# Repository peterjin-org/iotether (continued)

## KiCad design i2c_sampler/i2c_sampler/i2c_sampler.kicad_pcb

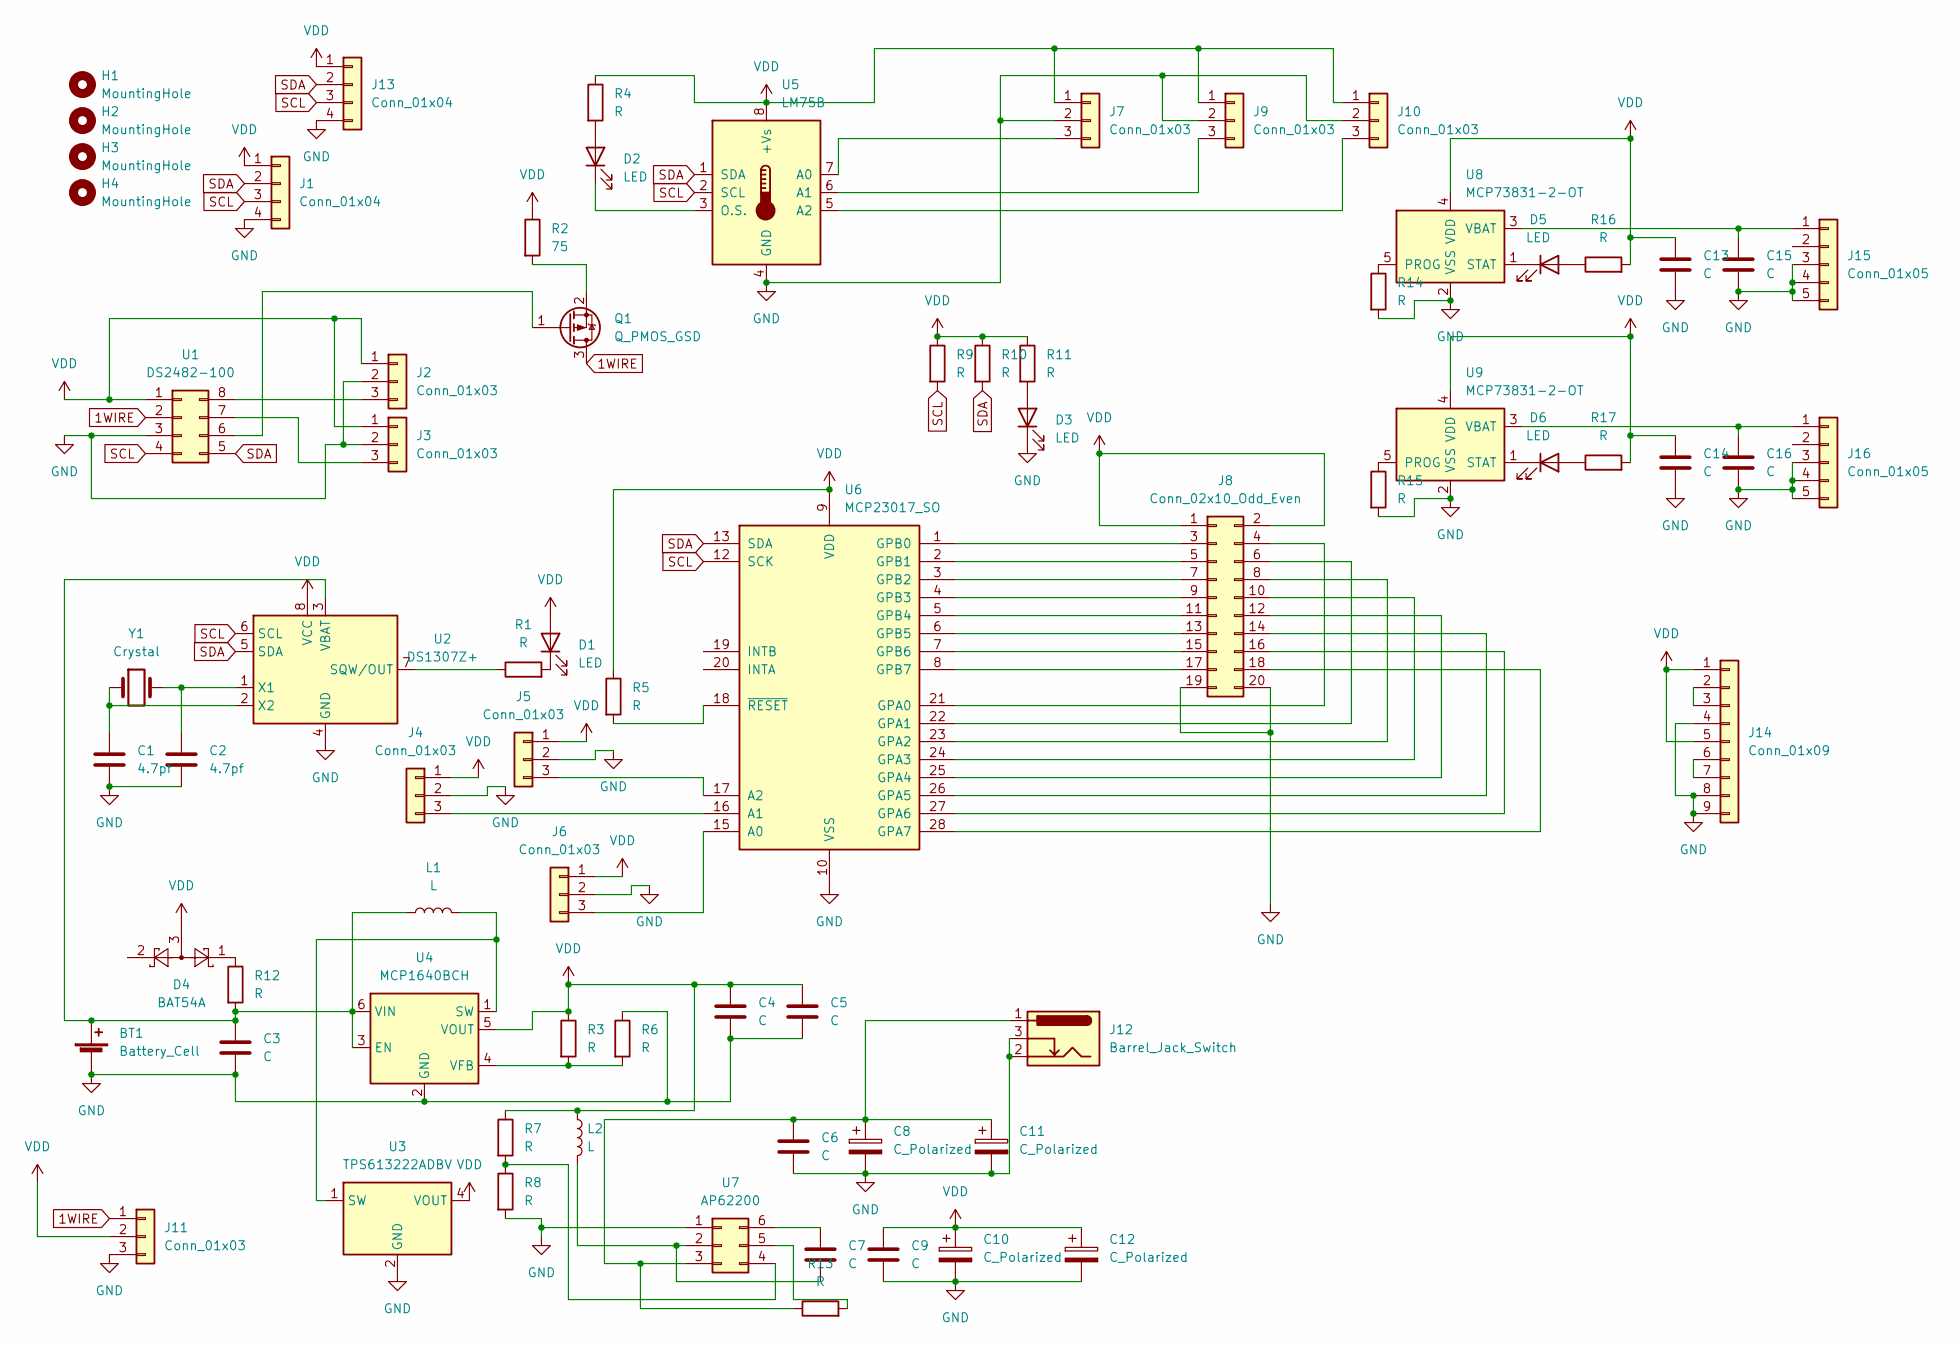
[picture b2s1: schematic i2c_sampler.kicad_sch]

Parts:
BT1: Battery_Cell; PinHeader_1x02_P2.54mm_Vertical
C1, C2: 4.7pf; C_0603_1608Metric
C3, C4, C5, C6, C7, C9, C13, C14, C15, C16: C; C_0805_2012Metric
C8, C10, C11, C12: C_Polarized; CP_Radial_D8.0mm_P3.50mm
D1, D2, D3: LED; LED_D5.0mm
D4: BAT54A; SOT-23
D5, D6: LED; LED_0603_1608Metric
H1, H2, H3, H4: MountingHole; MountingHole_3.2mm_M3
J1, J13: Conn_01x04; PinHeader_1x04_P2.54mm_Vertical
J2, J3, J4, J5, J6, J7, J9, J10: Conn_01x03; SOT-23-3
J8: Conn_02x10_Odd_Even; PinHeader_2x10_P2.54mm_Vertical
J11: Conn_01x03; PinHeader_1x03_P2.54mm_Vertical
J12: Barrel_Jack_Switch; BarrelJack_Horizontal
J14: Conn_01x09; USB_A_Wuerth_61400826021_Horizontal_Stacked
J15, J16: Conn_01x05; 009155003541006
L1: L; L_1210_3225Metric
L2: L; L_Radial_D10.5mm_P5.00mm_Abacron_AISR-01
Q1: Q_PMOS_GSD; SOT-23-3
R1, R3, R4, R5, R6, R7, R8, R9, R10, R11, R12, R13, R14, R15, R16, R17: R; R_0603_1608Metric
R2: 75; R_0805_2012Metric
U1: DS2482-100; SOIC-8_3.9x4.9mm_P1.27mm
U2: DS1307Z+; SOIC-8_3.9x4.9mm_P1.27mm
U3: TPS613222ADBV; SOT-23-5
U4: MCP1640BCH; SOT-23-6
U5: LM75B; SOIC-8_3.9x4.9mm_P1.27mm
U6: MCP23017_SO; SOIC-28W_7.5x17.9mm_P1.27mm
U7: AP62200; SOT-23-6
U8, U9: MCP73831-2-OT; SOT-23-5
Y1: Crystal; Crystal_Round_D2.0mm_Vertical

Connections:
1WIRE: J11.1, Q1.3 (D), U1.2
GND: BT1.2 (-), C1.2, C2.2, C3.2, C4.2, C5.2, C6.2, C8.2, C9.2, C10.2, C11.2, C12.2, C13.2, C14.2, C15.2, C16.2, D3.1 (K), J1.4, J2.2, J3.2, J4.2, J5.2, J6.2, J7.2, J8.19, J8.20, J9.2, J10.2, J11.3, J12.2, J12.3, J13.4, J14.4, J14.8, J14.9, J15.3, J15.4, J15.5, J16.3, J16.4, J16.5, R6.1, R8.2, R14.2, R15.2, U1.3, U2.4 (GND), U3.2 (GND), U4.2 (GND), U5.4 (GND), U6.10 (VSS), U7.1, U8.2 (VSS), U9.2 (VSS)
unnamed: BT1.1 (+), C3.1, L1.1, R12.2, U2.3 (VBAT), U4.3 (EN), U4.6 (VIN)
unnamed: C1.1, U2.2 (X2), Y1.1
unnamed: C2.1, U2.1 (X1), Y1.2
unnamed: C7.1, U7.6
unnamed: C7.2, L2.2, U7.2
unnamed: C6.1, C8.1, C11.1, J12.1, R13.1, U7.3
unnamed: C15.1, J15.1, U8.3 (VBAT)
unnamed: C16.1, J16.1, U9.3 (VBAT)
unnamed: D1.1 (K), R1.2
unnamed: D2.1 (K), U5.3 (O.S.)
unnamed: D2.2 (A), R4.2
unnamed: D3.2 (A), R11.2
unnamed: D4.1, R12.1
unnamed: D5.1 (K), U8.1 (STAT)
unnamed: D5.2 (A), R16.1
unnamed: D6.1 (K), U9.1 (STAT)
unnamed: D6.2 (A), R17.1
unnamed: J2.3, U1.8
unnamed: J3.3, U1.7
unnamed: J4.3, U6.16 (A1)
unnamed: J5.3, U6.17 (A2)
unnamed: J6.3, U6.15 (A0)
unnamed: J7.3, U5.7 (A0)
unnamed: J8.3, U6.1 (GPB0)
unnamed: J8.4, U6.21 (GPA0)
unnamed: J8.5, U6.2 (GPB1)
unnamed: J8.6, U6.22 (GPA1)
unnamed: J8.7, U6.3 (GPB2)
unnamed: J8.8, U6.23 (GPA2)
unnamed: J8.9, U6.4 (GPB3)
unnamed: J8.10, U6.24 (GPA3)
unnamed: J8.11, U6.5 (GPB4)
unnamed: J8.12, U6.25 (GPA4)
unnamed: J8.13, U6.6 (GPB5)
unnamed: J8.14, U6.26 (GPA5)
unnamed: J8.15, U6.7 (GPB6)
unnamed: J8.16, U6.27 (GPA6)
unnamed: J8.17, U6.8 (GPB7)
unnamed: J8.18, U6.28 (GPA7)
unnamed: J9.3, U5.6 (A1)
unnamed: J10.3, U5.5 (A2)
unnamed: J14.2, J14.3
unnamed: J14.6, J14.7
unnamed: L1.2, U3.1 (SW), U4.1 (SW)
unnamed: Q1.1 (G), U1.6
unnamed: Q1.2 (S), R2.2
unnamed: R1.1, U2.7 (SQW/OUT)
unnamed: R3.2, R6.2, U4.4 (VFB)
unnamed: R5.2, U6.18 (~RESET)
unnamed: R7.2, R8.1, U7.4
unnamed: R13.2, U7.5
unnamed: R14.1, U8.5 (PROG)
unnamed: R15.1, U9.5 (PROG)
SCL: J1.3, J13.3, R9.2, U1.4, U2.6 (SCL), U5.2 (SCL), U6.12 (SCK)
SDA: J1.2, J13.2, R10.2, U1.5, U2.5 (SDA), U5.1 (SDA), U6.13 (SDA)
VDD: C4.1, C5.1, C9.1, C10.1, C12.1, C13.1, C14.1, D1.2 (A), D4.3, J1.1, J2.1, J3.1, J4.1, J5.1, J6.1, J7.1, J8.1, J8.2, J9.1, J10.1, J11.2, J13.1, J14.1, J14.5, L2.1, R2.1, R3.1, R4.1, R5.1, R7.1, R9.1, R10.1, R11.1, R16.2, R17.2, U1.1, U2.8 (VCC), U3.4 (VOUT), U4.5 (VOUT), U5.8 (+Vs), U6.9 (VDD), U8.4 (VDD), U9.4 (VDD)

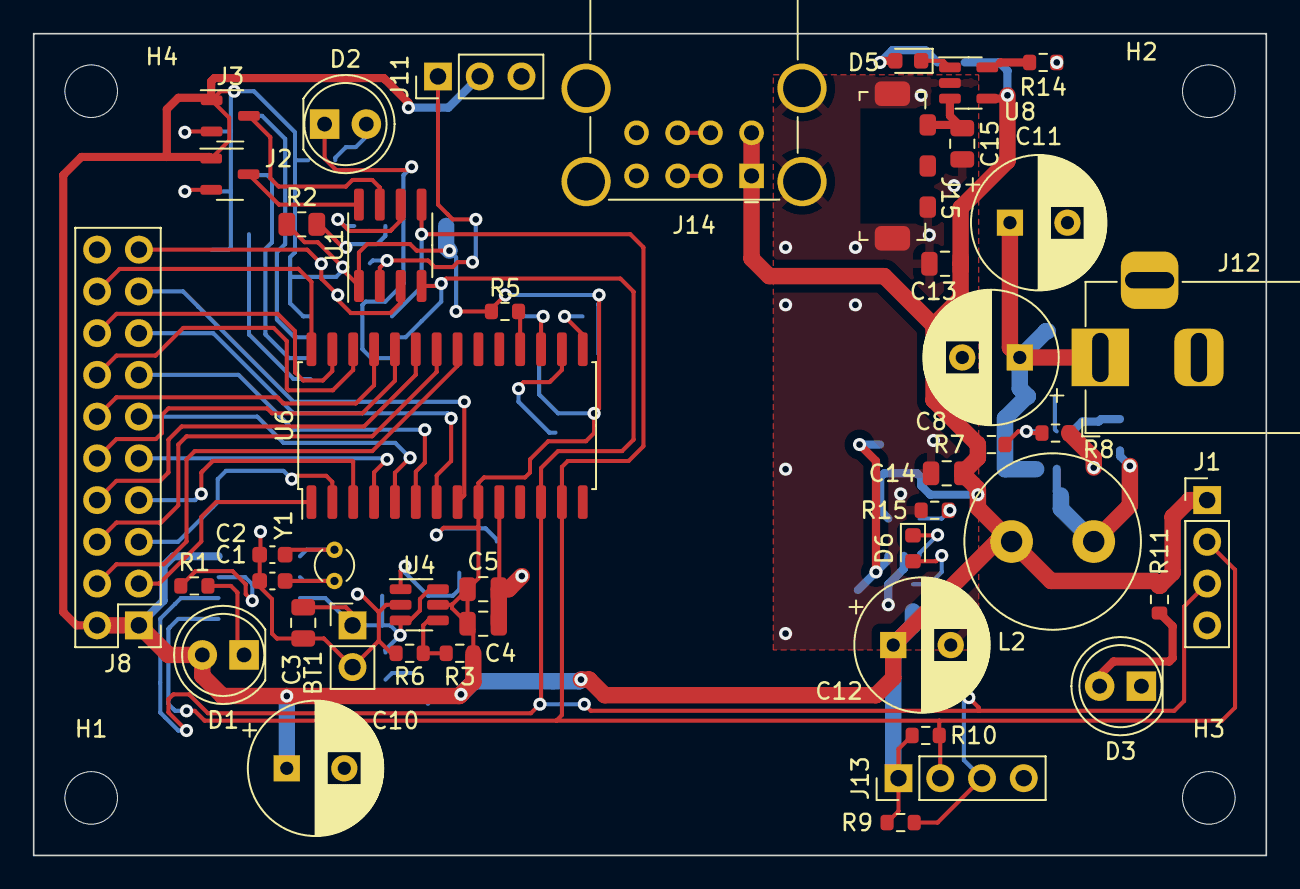
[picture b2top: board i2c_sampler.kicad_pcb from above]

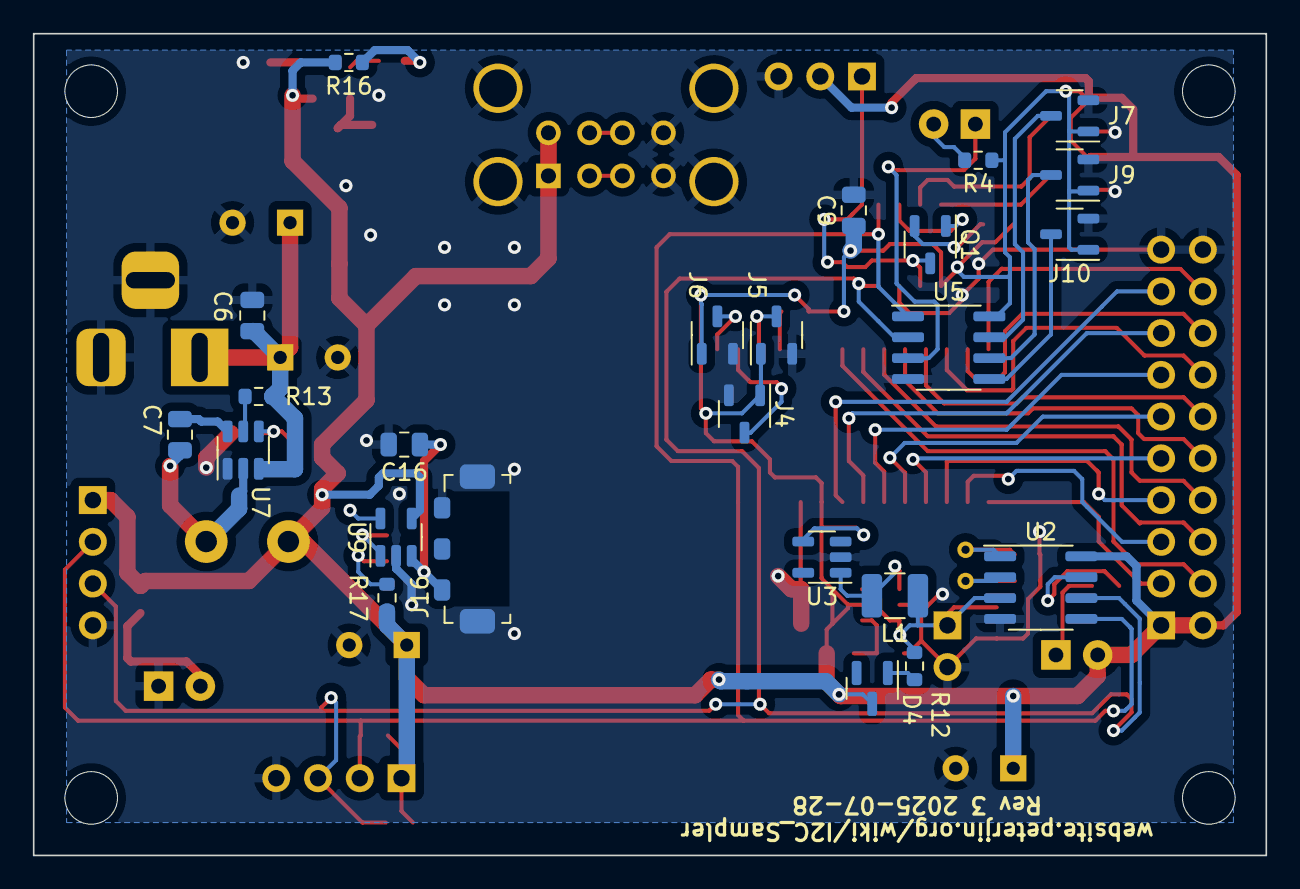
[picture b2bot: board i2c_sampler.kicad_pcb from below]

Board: 2 copper layers, 75.0 x 50.0 mm, 73 parts (24 on the bottom side), 58 nets.

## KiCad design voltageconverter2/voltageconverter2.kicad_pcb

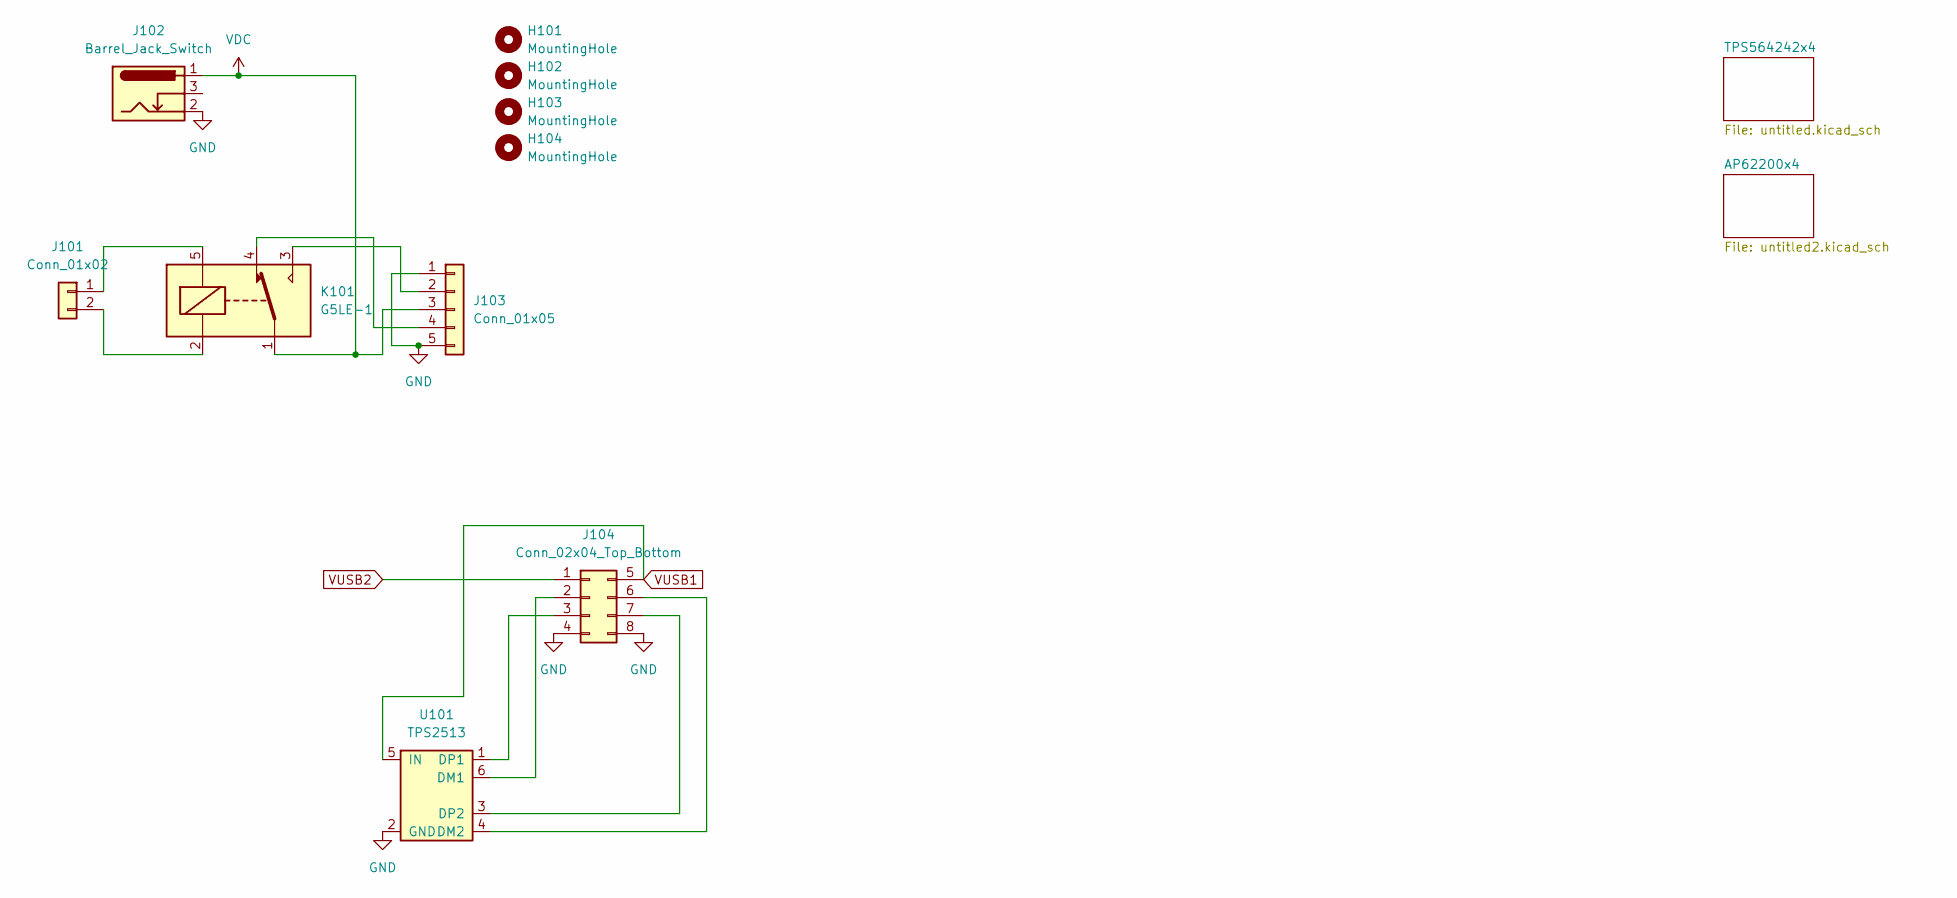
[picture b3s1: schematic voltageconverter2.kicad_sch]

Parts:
H101, H102, H103, H104: MountingHole; MountingHole_3.2mm_M3
J101: Conn_01x02; PinHeader_1x02_P2.54mm_Vertical
J102: Barrel_Jack_Switch; BarrelJack_Horizontal
J103: Conn_01x05; TerminalBlock_bornier-5_P5.08mm
J104: Conn_02x04_Top_Bottom; USB_A_Wuerth_61400826021_Horizontal_Stacked
K101: G5LE-1; Relay_SPDT_Omron-G5LE-1
U101: TPS2513; SOT-23-6

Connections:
GND: J102.2, J103.1, J103.5, J104.4, J104.8, U101.2 (GND); also elsewhere on the board
unnamed: J101.1, K101.5
unnamed: J101.2, K101.2
unnamed: J103.2, K101.3
unnamed: J103.4, K101.4
unnamed: J104.2, U101.6 (DM1)
unnamed: J104.3, U101.1 (DP1)
unnamed: J104.6, U101.4 (DM2)
unnamed: J104.7, U101.3 (DP2)
VDC: J102.1, J103.3, K101.1; also elsewhere on the board
VUSB1: J104.5, U101.5 (IN); also elsewhere on the board
VUSB2: J104.1; also elsewhere on the board

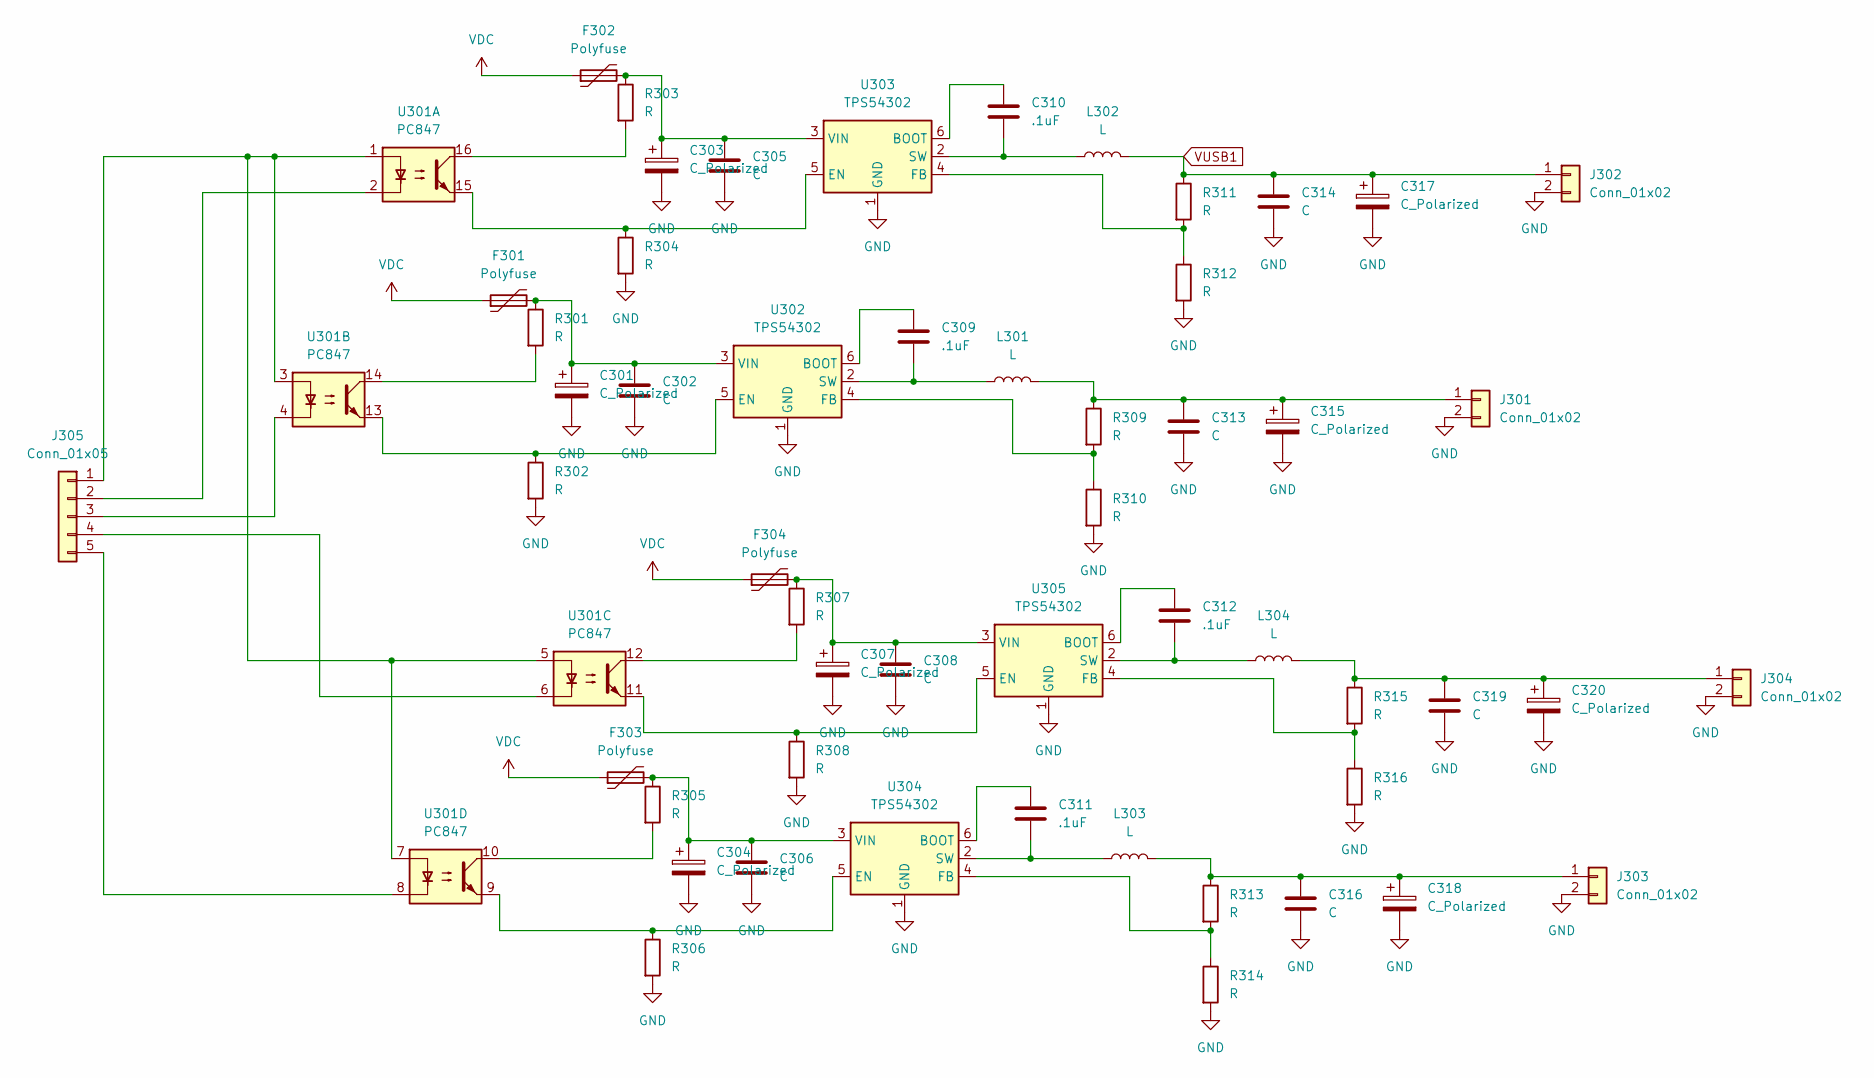
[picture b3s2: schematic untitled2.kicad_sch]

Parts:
C301, C303, C304, C307, C315, C317, C318, C320: C_Polarized; CP_Radial_D8.0mm_P3.50mm
C302, C305, C306, C308, C313, C314, C316, C319: C; C_0805_2012Metric
C309, C310, C311, C312: .1uF; C_0603_1608Metric
F301, F302, F303, F304: Polyfuse; Fuse_Bourns_MF-RG800
J301, J302, J303, J304: Conn_01x02; TerminalBlock_bornier-2_P5.08mm
J305: Conn_01x05; PinHeader_1x05_P2.54mm_Vertical
L301, L302, L303, L304: L; L_Radial_D10.0mm_P5.00mm_Fastron_07M
R301, R302, R303, R304, R305, R306, R307, R308, R309, R310, R311, R312, R313, R314, R315, R316: R; R_0603_1608Metric
U301: PC847; DIP-16_W7.62mm
U302, U303, U304, U305: TPS54302; SOT-23-6

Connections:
GND: C301.2, C302.2, C303.2, C304.2, C305.2, C306.2, C307.2, C308.2, C313.2, C314.2, C315.2, C316.2, C317.2, C318.2, C319.2, C320.2, J301.2, J302.2, J303.2, J304.2, R302.2, R304.2, R306.2, R308.2, R310.2, R312.2, R314.2, R316.2, U302.1 (GND), U303.1 (GND), U304.1 (GND), U305.1 (GND); also elsewhere on the board
unnamed: C301.1, C302.1, F301.2, R301.1, U302.3 (VIN)
unnamed: C303.1, C305.1, F302.2, R303.1, U303.3 (VIN)
unnamed: C304.1, C306.1, F303.2, R305.1, U304.3 (VIN)
unnamed: C307.1, C308.1, F304.2, R307.1, U305.3 (VIN)
unnamed: C309.1, U302.6 (BOOT)
unnamed: C309.2, L301.1, U302.2 (SW)
unnamed: C310.1, U303.6 (BOOT)
unnamed: C310.2, L302.1, U303.2 (SW)
unnamed: C311.1, U304.6 (BOOT)
unnamed: C311.2, L303.1, U304.2 (SW)
unnamed: C312.1, U305.6 (BOOT)
unnamed: C312.2, L304.1, U305.2 (SW)
unnamed: C313.1, C315.1, J301.1, L301.2, R309.1
unnamed: C316.1, C318.1, J303.1, L303.2, R313.1
unnamed: C319.1, C320.1, J304.1, L304.2, R315.1
unnamed: J305.1, U301.1, U301.3, U301.5, U301.7
unnamed: J305.2, U301.2
unnamed: J305.3, U301.4
unnamed: J305.4, U301.6
unnamed: J305.5, U301.8
unnamed: R301.2, U301.14
unnamed: R302.1, U301.13, U302.5 (EN)
unnamed: R303.2, U301.16
unnamed: R304.1, U301.15, U303.5 (EN)
unnamed: R305.2, U301.10
unnamed: R306.1, U301.9, U304.5 (EN)
unnamed: R307.2, U301.12
unnamed: R308.1, U301.11, U305.5 (EN)
unnamed: R309.2, R310.1, U302.4 (FB)
unnamed: R311.2, R312.1, U303.4 (FB)
unnamed: R313.2, R314.1, U304.4 (FB)
unnamed: R315.2, R316.1, U305.4 (FB)
VDC: F301.1, F302.1, F303.1, F304.1; also elsewhere on the board
VUSB1: C314.1, C317.1, J302.1, L302.2, R311.1; also elsewhere on the board

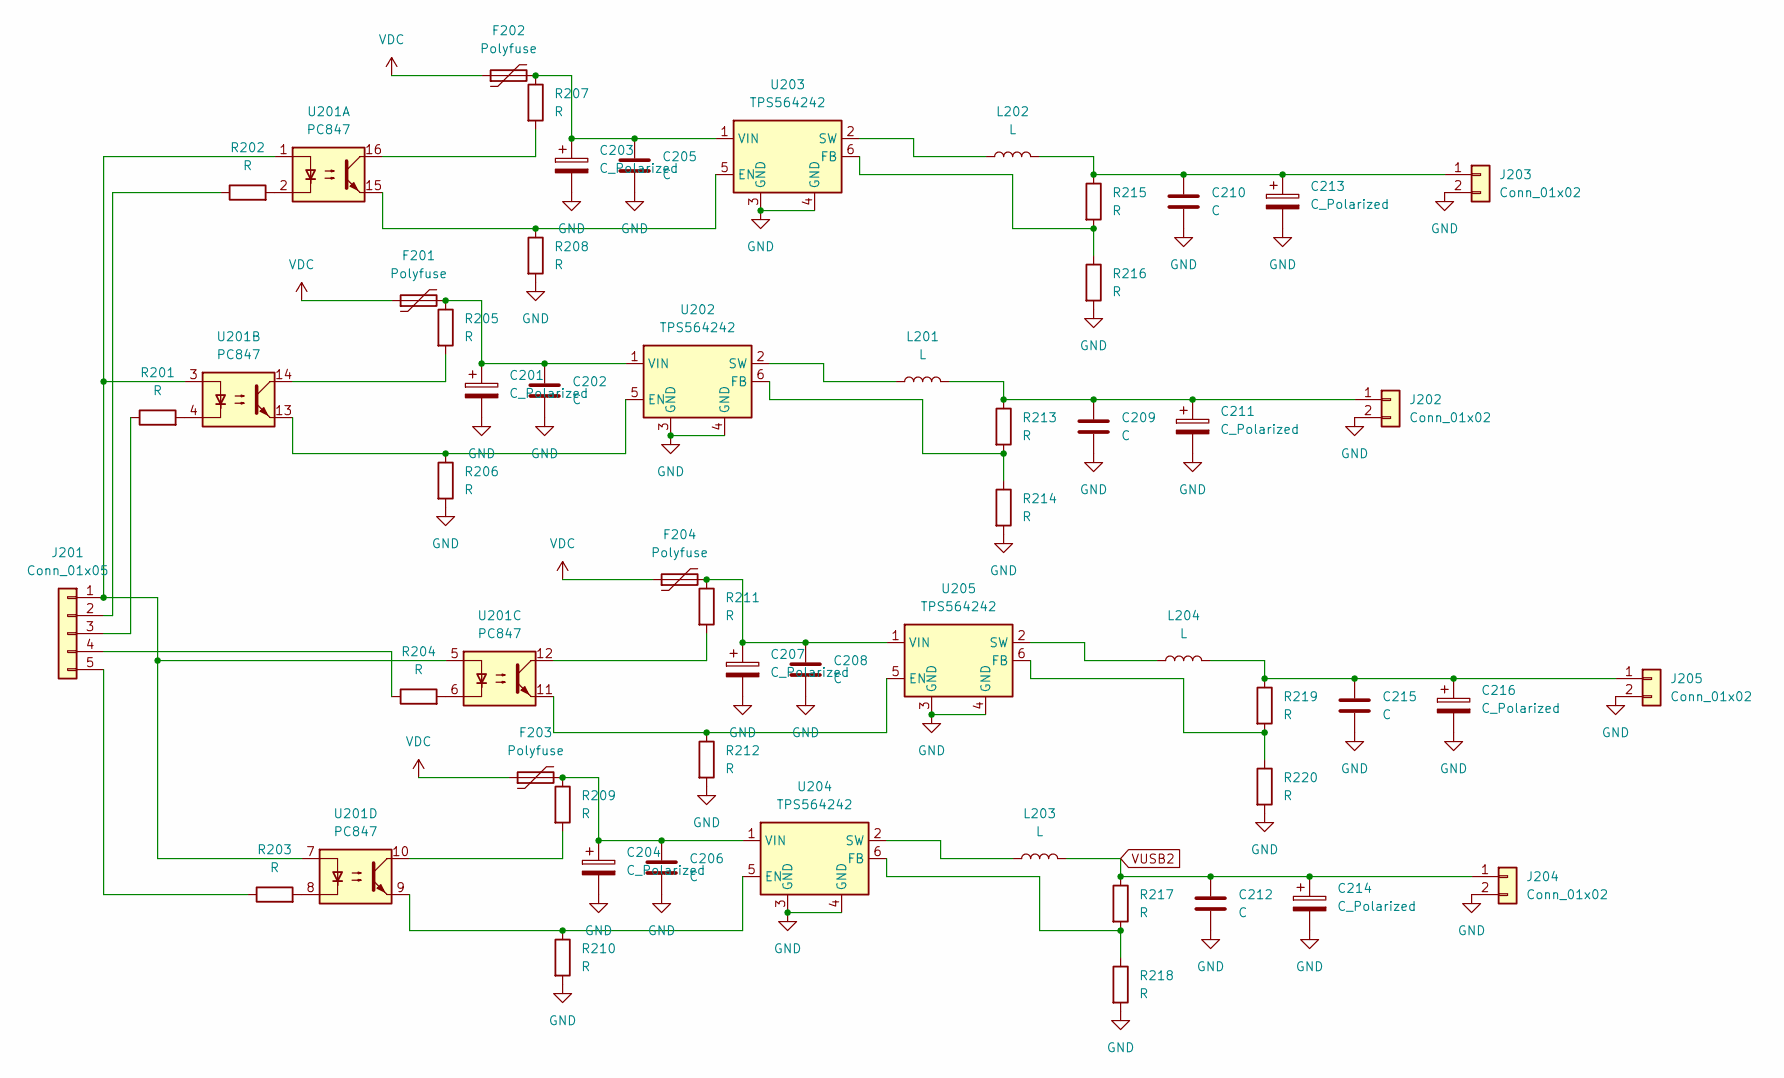
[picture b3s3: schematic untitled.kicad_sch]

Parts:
C201, C203, C204, C207, C211, C213, C214, C216: C_Polarized; CP_Radial_D8.0mm_P3.50mm
C202, C205, C206, C208, C209, C210, C212, C215: C; C_0805_2012Metric
F201, F202, F203, F204: Polyfuse; Fuse_Bourns_MF-RG800
J201: Conn_01x05; PinHeader_1x05_P2.54mm_Vertical
J202, J203, J204, J205: Conn_01x02; TerminalBlock_bornier-2_P5.08mm
L201, L202, L203, L204: L; L_Radial_D10.0mm_P5.00mm_Fastron_07M
R201, R202, R203, R204, R205, R206, R207, R208, R209, R210, R211, R212, R213, R214, R215, R216, R217, R218, R219, R220: R; R_0603_1608Metric
U201: PC847; DIP-16_W7.62mm
U202, U203, U204, U205: TPS564242; SOT-563_smallpads

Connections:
GND: C201.2, C202.2, C203.2, C204.2, C205.2, C206.2, C207.2, C208.2, C209.2, C210.2, C211.2, C212.2, C213.2, C214.2, C215.2, C216.2, J202.2, J203.2, J204.2, J205.2, R206.2, R208.2, R210.2, R212.2, R214.2, R216.2, R218.2, R220.2, U202.3 (GND), U202.4 (GND), U203.3 (GND), U203.4 (GND), U204.3 (GND), U204.4 (GND), U205.3 (GND), U205.4 (GND); also elsewhere on the board
unnamed: C201.1, C202.1, F201.2, R205.1, U202.1 (VIN)
unnamed: C203.1, C205.1, F202.2, R207.1, U203.1 (VIN)
unnamed: C204.1, C206.1, F203.2, R209.1, U204.1 (VIN)
unnamed: C207.1, C208.1, F204.2, R211.1, U205.1 (VIN)
unnamed: C209.1, C211.1, J202.1, L201.2, R213.1
unnamed: C210.1, C213.1, J203.1, L202.2, R215.1
unnamed: C215.1, C216.1, J205.1, L204.2, R219.1
unnamed: J201.1, U201.1, U201.3, U201.5, U201.7
unnamed: J201.2, R202.1
unnamed: J201.3, R201.1
unnamed: J201.4, R204.1
unnamed: J201.5, R203.1
unnamed: L201.1, U202.2 (SW)
unnamed: L202.1, U203.2 (SW)
unnamed: L203.1, U204.2 (SW)
unnamed: L204.1, U205.2 (SW)
unnamed: R201.2, U201.4
unnamed: R202.2, U201.2
unnamed: R203.2, U201.8
unnamed: R204.2, U201.6
unnamed: R205.2, U201.14
unnamed: R206.1, U201.13, U202.5 (EN)
unnamed: R207.2, U201.16
unnamed: R208.1, U201.15, U203.5 (EN)
unnamed: R209.2, U201.10
unnamed: R210.1, U201.9, U204.5 (EN)
unnamed: R211.2, U201.12
unnamed: R212.1, U201.11, U205.5 (EN)
unnamed: R213.2, R214.1, U202.6 (FB)
unnamed: R215.2, R216.1, U203.6 (FB)
unnamed: R217.2, R218.1, U204.6 (FB)
unnamed: R219.2, R220.1, U205.6 (FB)
VDC: F201.1, F202.1, F203.1, F204.1; also elsewhere on the board
VUSB2: C212.1, C214.1, J204.1, L203.2, R217.1; also elsewhere on the board

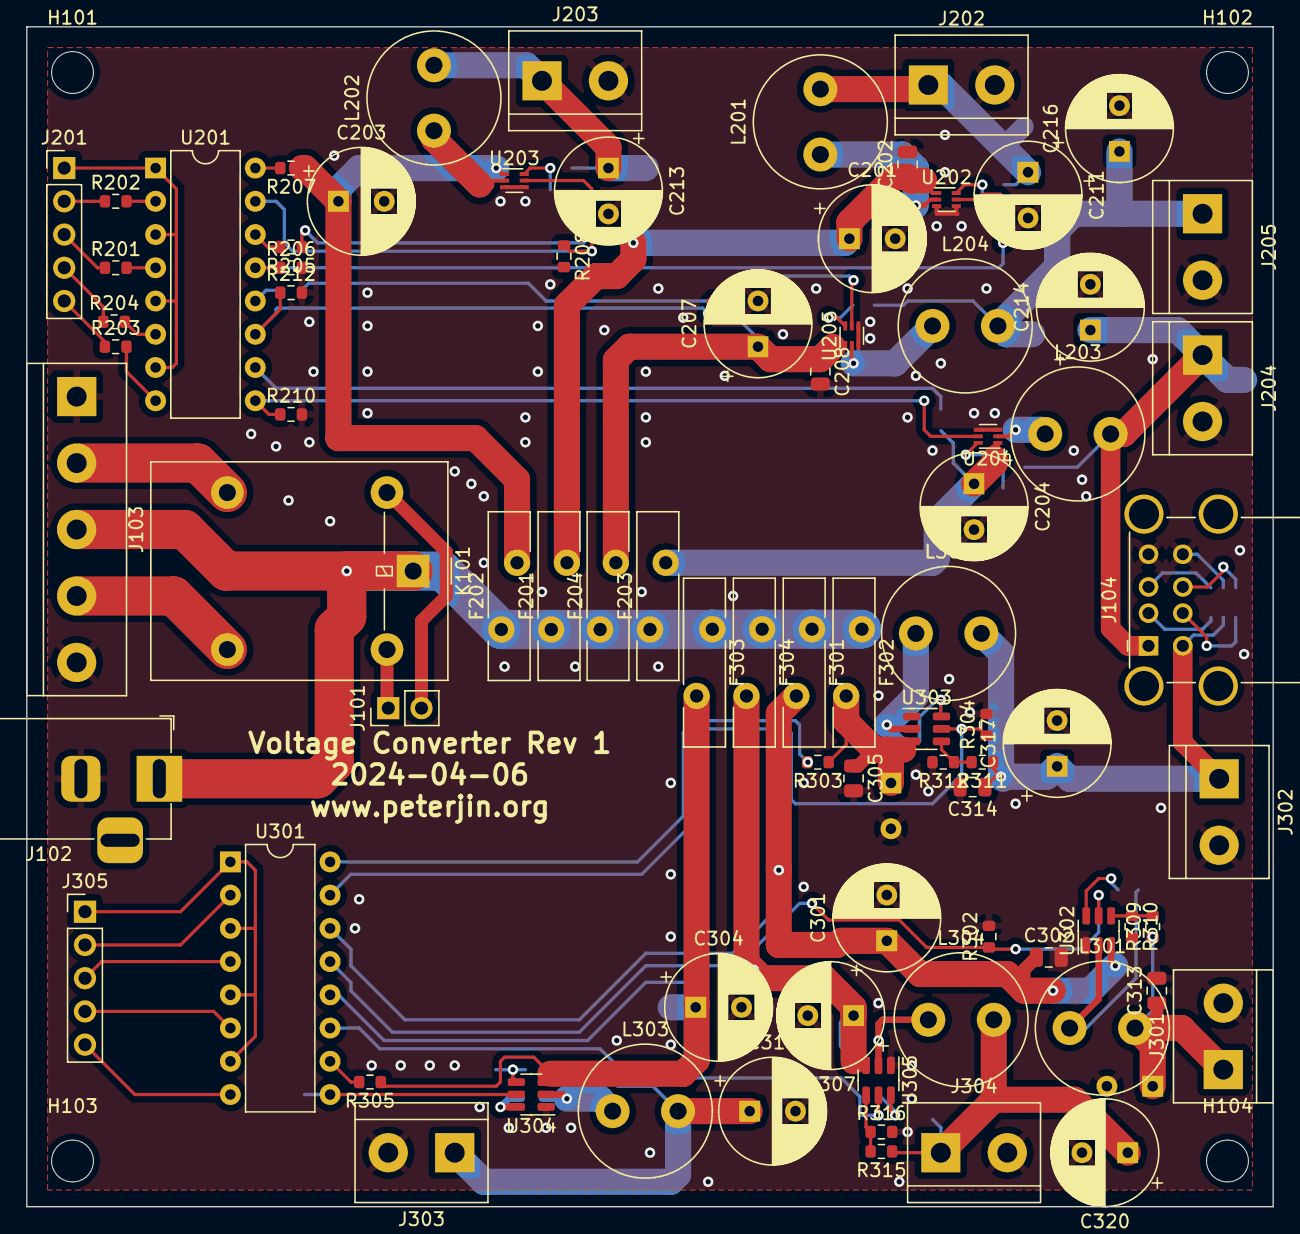
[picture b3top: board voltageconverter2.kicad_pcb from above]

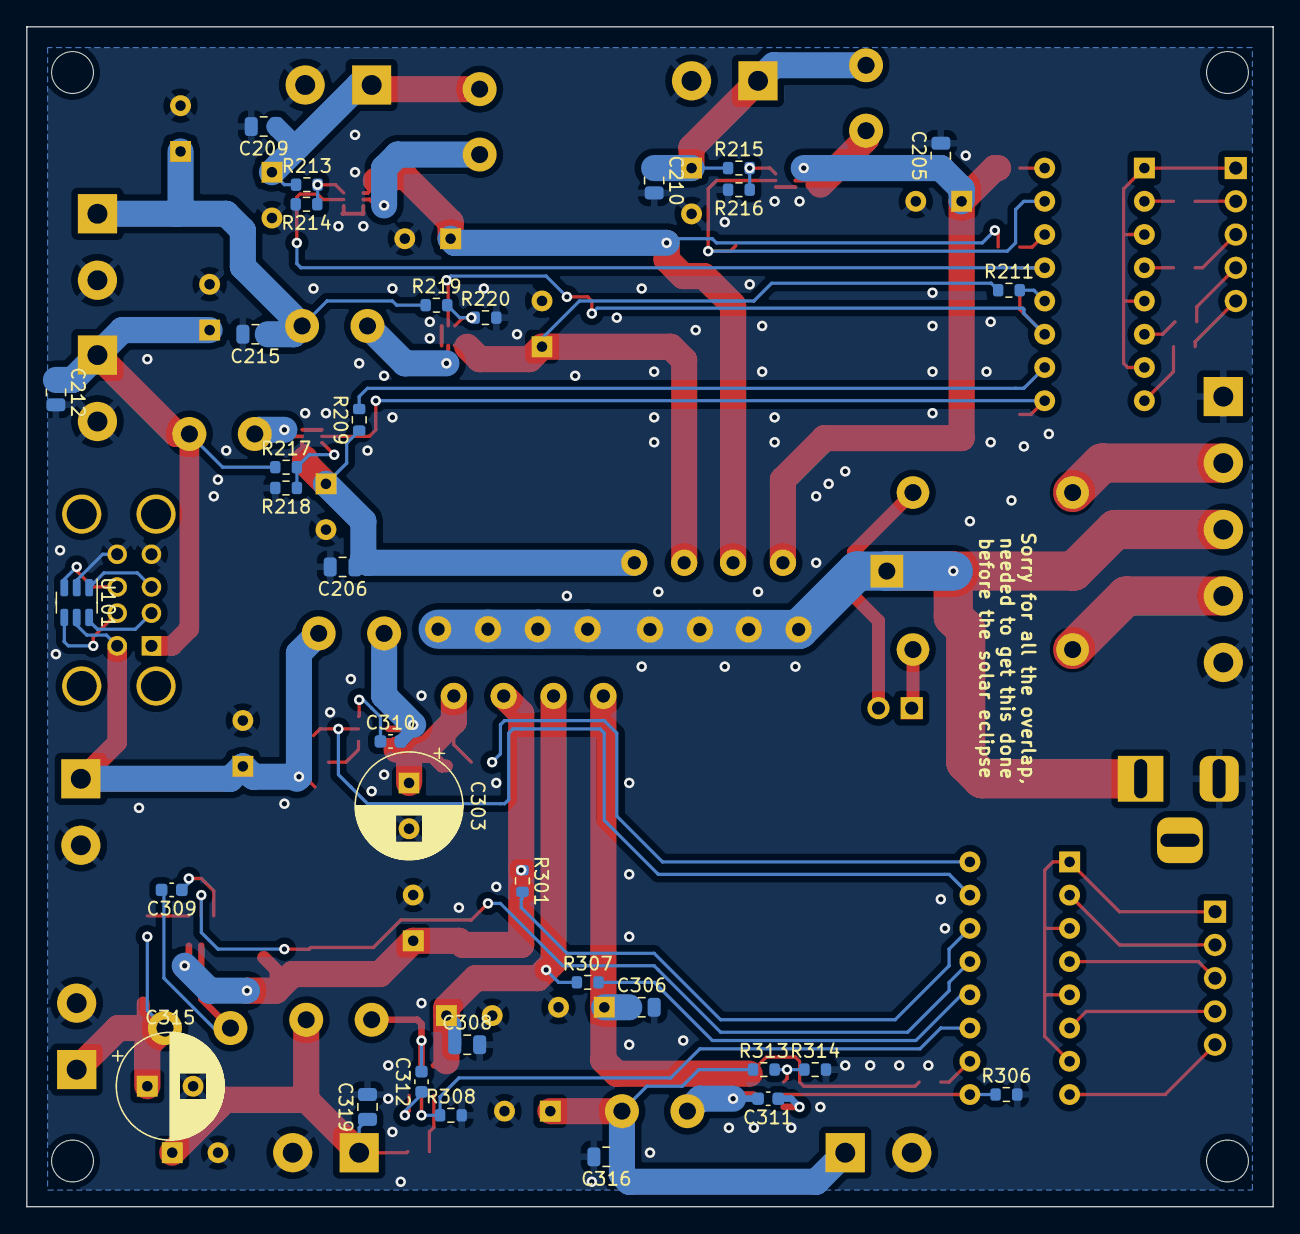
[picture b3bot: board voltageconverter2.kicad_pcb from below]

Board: 2 copper layers, 95.2 x 90.2 mm, 118 parts (33 on the bottom side), 76 nets.
